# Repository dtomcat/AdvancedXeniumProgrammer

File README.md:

# OpenXenium JTAG and Flash Memory Chip programmer

**This is based on work done by [kooscode](https://github.com/kooscode/xenium-programmer) and [Ryzee119](https://github.com/ryzee119/openxenium) with modifications to program the bare ICs.  Most of the code here was done by kooscode (please visit the link above).

--------------

## * Read: ["Home Brew" on ORIGINAL XBOX](XBOX.md) - a detailed article on why and how *

The tools in this repo will allow you to use a Raspberry PI to program the CPLD and Flash Memory chips of the OpenXenium via Jtag and a custom 4-bit bus NOR Flash programming protocol.
Original project mentioned above allowed the use of an Onion Omega2+... This has been removed for this project. 

### Raspberry PI:
- This has only been tested on PI Zero W and PI 3B+ models so far.

https://www.pishop.us/product/raspberry-pi-zero-w/

-------------
## INSTALLING THE XENIUM PROGRAMMER
**The scripts assumes user of "pi"...  if using a different user, you'll need to manually change "pi" to your username in the scripts**
- After the OS has been written to your SD card, insert SD card into PC.
    - Add the following to the last line in "config.txt":   `enable_uart=1`
        - This is required to allow the PWR LED to function properly.
- Save edit and eject SD Card.  Insert SD card into Pi and boot up.
- Connect to the PI via SSH or Serial terminal
- If git is not installed, you need to install it:
    - `sudo apt-get install git`
- Clone this repo by running: `git clone https://github.com/dtomcat/AdvancedXeniumProgrammer.git`
- Change to program directory: `cd AdvancedXeniumProgrammer`
- Fix permission on install file:  `chmod 755 install`
- Then run: `./install`
- Setup service to listen for button presses:
    - `sudo cp xenium.service /etc/systemd/system/xenium.service`
    - `sudo systemctl daemon-reload`
    - `sudo systemctl enable xenium`
    - `sudo service xenium start`

## UPDATING XENIUM PROGRAMMER

- Connect to the PI via SSH or Serial terminal 
- Pull the latest code with: `git pull`
- Then run: `./install` 

-------------
## STATUS LED MEANING (From top to bottom)

- First:  Programming CPLD with BIT BANG firmware
- Second: Programming Flash with specified OS
- Third:  Verifying flash was programmed successfully
- Forth:  Programing CPLD with OpenXenium firmware

-------------
## PROGRAMMING THE XENIUM CPLD AND/OR FLASH MEMORY (STANDALONE)

Note: You will need to provide your own PrometheOS bin file. (save it in the /xenium-bin folder as promOS.bin)

- After the PI has fully booted and the green led is on...
    - Press the FIRST button to program the OpenXenium with XeniumOS.
    - Hold the FIRST button to program the OpenXenium with PrometheOS.
    - Press the SECOND button to program the flash chip with XeniumOS. (**The CPLD must be programmed with the Bit Bang firmware or this will fail.)
    - Hold the SECOND button to program the flash chip with PrometheOS. (**The CPLD must be programmed with the Bit Bang firmware or this will fail.)
    - Press the THIRD button to program the CPLD with the OpenXenium Firmware.
    - Hold the THIRD button to program the CPLD with the BitBang Firmware.
    - Press the FOURTH button to clear any errors.
    - Hold the FOURTH button to shutdown the Raspberry Pi.

-------------
## PROGRAMMING THE XENIUM CPLD AND/OR FLASH MEMORY (SSH/SERIAL)
This is good to do if you keep getting an error trying to program the chips. (Red LED remains on)

Note: You will need to provide your own PrometheOS bin file. (save it in the /xenium-bin folder as promOS.bin)

- Connect to the PI via SSH or Serial terminal
- Change dir to AdvancedXeniumProgrammer
- You can program CPLD and FLASH in one single step with XeniumOS (XOS).
    - Run: `./xenium-programmer-smd`
- You can program CPLD and FLASH in one single step with PrometheOS (PromOS).
    - Run: `./PromOS-programmer-smd`
- You can program just the CPLD in one two ways.
    - To program the Bit Bang firmware: 
        - Run: `./BitBangOnly`
    - To program the OpenXenium firmware: 
        - Run: `./OX-Only_SMD`
- You can program just the Flash in oe of two ways. (The CPLD MUST have the Bit Bang Firmware loaded)
    - To program XOS:
          - Run: `./FlashOnly`
    - To program PromOS:
          - Run: `./FlashOnlyProm`

-------------
### 3D PRINTED CASE

Just a quick and simple design I put together.  I'm sure this thing could be improved upon greatly.  Sharing for anyone wanting it.

NOTE:  for the "light pipes", I just used some clear PLA (2.90mm not standard 1.75) filament. 

--------------
### PC BOARD

Huge thanks to James Bolding for the Original Eagle PCB hardware design!
This PCB design is based on his original work.  

- You can use the FREE Eagle PCB to load this up or just use the gerber files to have the PCB made at OSH Park!

--------------

### PARTS NOT LISTED IN BOM
There are a couple parts not listed in BOM that could be helpful.
- Pin headers 2.54 spacing
    - 1 2x7 for LPC port
    - 1 1x2 for 3v3 (Optionally... but connect two points with solder)
        - Will need a 2-Pin Jumper/Bridge Cap if installing 1x2 pin header
- 6 Pogo pins (P75-E3 pogo pins seem to work the best)

-------------
## CREDITS

- Koos du Preez - Creator (kdupreez@hotmail.com - Comments, improvements, critique, etc. is welcome!)
- Dtomcat - SMD programmer PCB design and code split to allow status LEDs.
- James Bolding - Orignal hardware design and PCB!
- Ryzee119 -  OpenXenium Firmware and hardware and all round awesomeness!
- XC3SPROG - Not sure who to thank here, but the source code was pivotal in making this work!

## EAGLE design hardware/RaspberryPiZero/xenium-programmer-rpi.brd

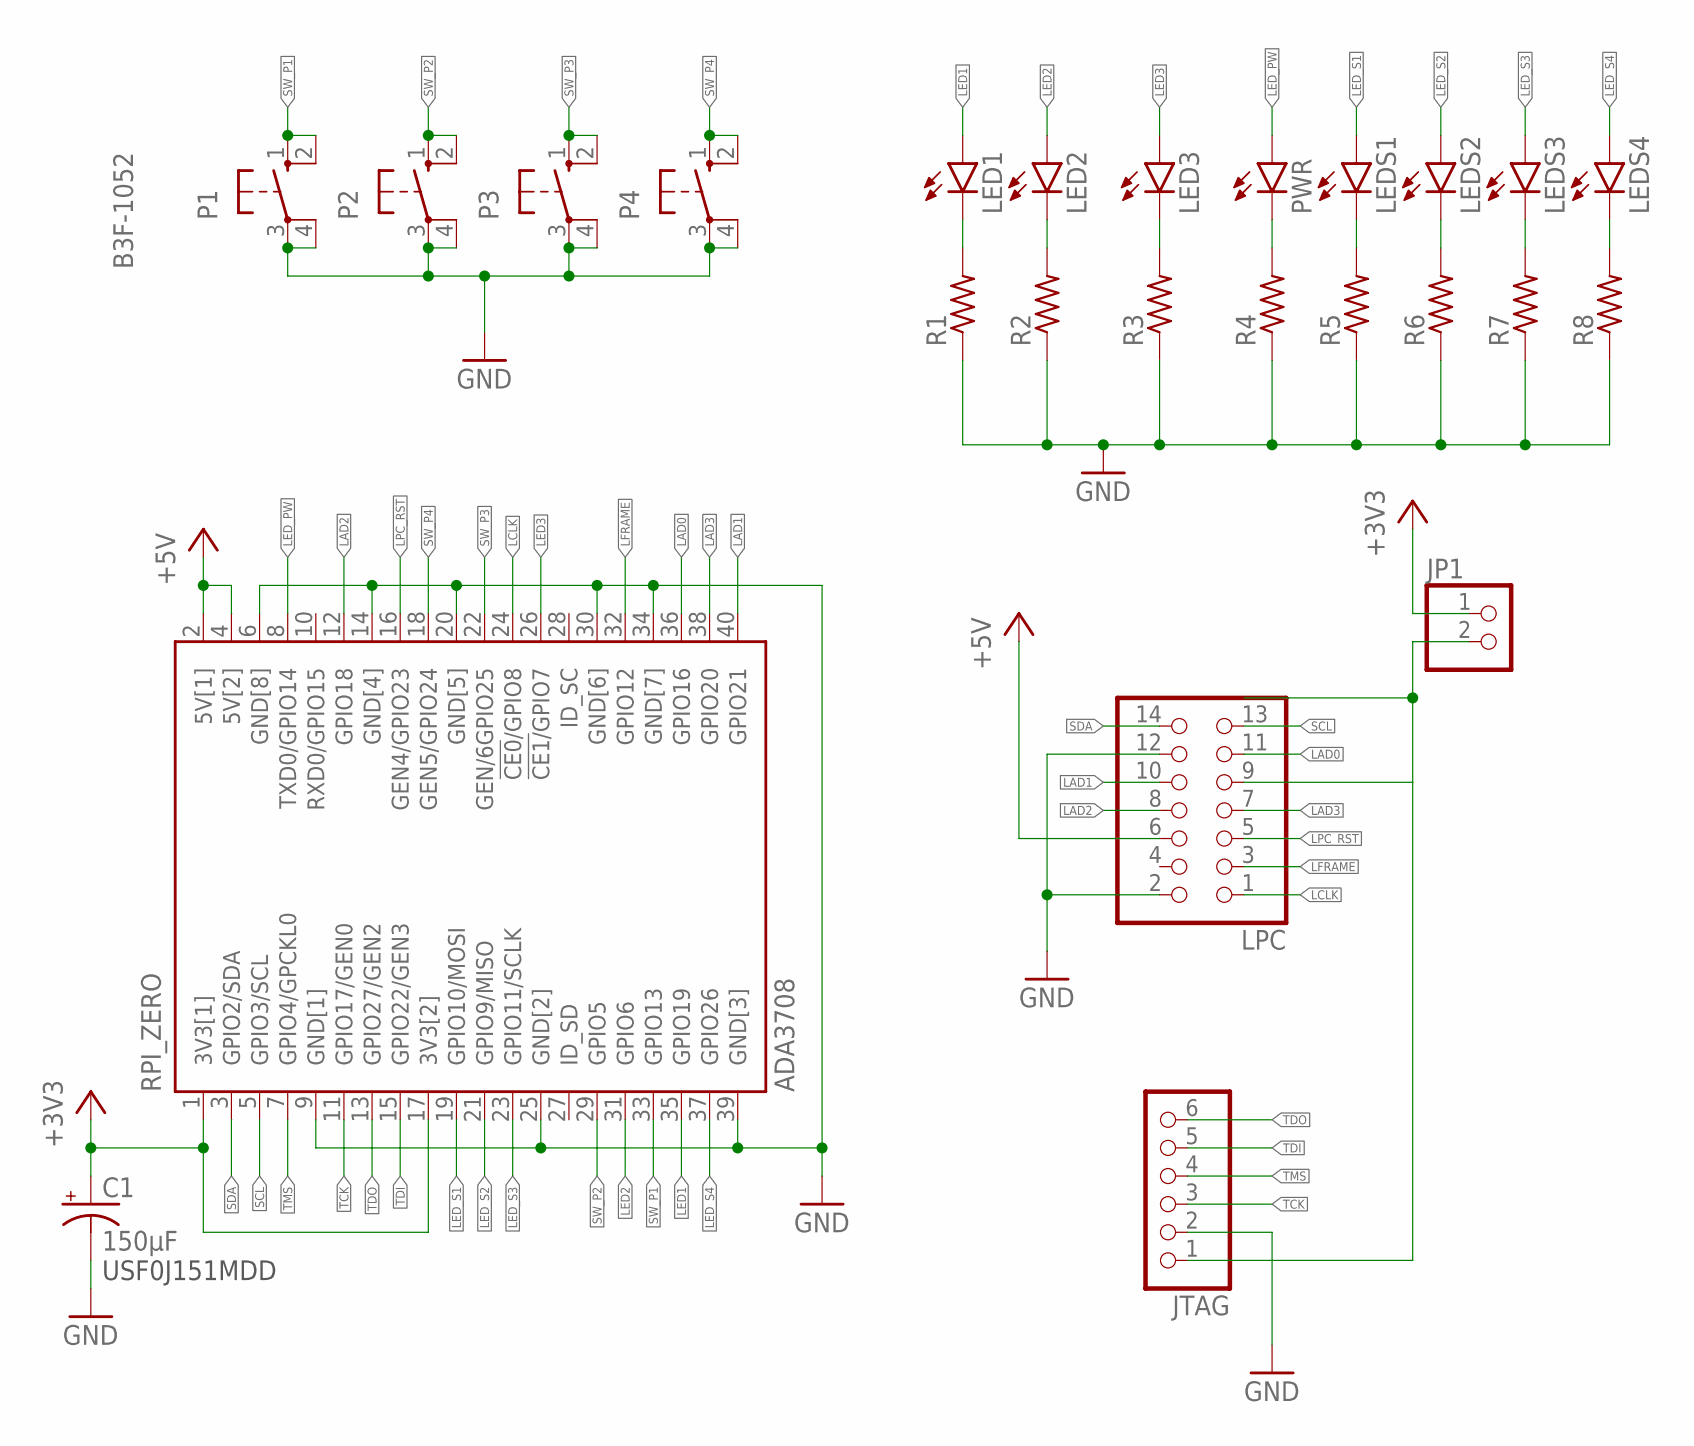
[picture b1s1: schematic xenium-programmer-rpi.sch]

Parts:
C1: 150µF; E3,5-8
JP1: PINHD-1X2; 1X02
JTAG: PINHD-1X6; 1X06
LED1, LED2, LED3: LEDCHIPLED_1206; CHIPLED_1206
LEDS1, LEDS2, LEDS3, LEDS4: LEDCHIPLED_1206; CHIPLED_1206
LPC: PINHD-2X7; 2X07
P1, P2, P3, P4: B3F-1052; B3F-10XX
PWR: LEDCHIPLED_1206; CHIPLED_1206
R1, R2, R3, R4, R5, R6, R7, R8: R-US_R1206; R1206
RPI_ZERO: ADA3708; ADA3708_RPI-ZERO

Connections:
+3V3: C1.+, JP1.1, RPI_ZERO.1 (3V3[1]), RPI_ZERO.17 (3V3[2])
+5V: LPC.6, RPI_ZERO.2 (5V[1]), RPI_ZERO.4 (5V[2])
GND: C1.-, JTAG.2, LPC.2, LPC.12, P1.3, P1.4 (P1), P2.3, P2.4 (P1), P3.3, P3.4 (P1), P4.3, P4.4 (P1), R1.1, R2.1, R3.1, R4.1, R5.1, R6.1, R7.1, R8.1, RPI_ZERO.6 (GND[8]), RPI_ZERO.9 (GND[1]), RPI_ZERO.14 (GND[4]), RPI_ZERO.20 (GND[5]), RPI_ZERO.25 (GND[2]), RPI_ZERO.30 (GND[6]), RPI_ZERO.34 (GND[7]), RPI_ZERO.39 (GND[3])
LAD0: LPC.11, RPI_ZERO.36 (GPIO16)
LAD1: LPC.10, RPI_ZERO.40 (GPIO21)
LAD2: LPC.8, RPI_ZERO.12 (GPIO18)
LAD3: LPC.7, RPI_ZERO.38 (GPIO20)
LCLK: LPC.1, RPI_ZERO.24 (!CE0!/GPIO8)
LED1: LED1.A, RPI_ZERO.35 (GPIO19)
LED2: LED2.A, RPI_ZERO.31 (GPIO6)
LED3: LED3.A, RPI_ZERO.26 (!CE1/!GPIO7)
LED_PW: PWR.A, RPI_ZERO.8 (TXD0/GPIO14)
LED_S1: LEDS1.A, RPI_ZERO.19 (GPIO10/MOSI)
LED_S2: LEDS2.A, RPI_ZERO.21 (GPIO9/MISO)
LED_S3: LEDS3.A, RPI_ZERO.23 (GPIO11/SCLK)
LED_S4: LEDS4.A, RPI_ZERO.37 (GPIO26)
LFRAME: LPC.3, RPI_ZERO.32 (GPIO12)
LPC_RST: LPC.5, RPI_ZERO.16 (GEN4/GPIO23)
unnamed: LED1.C, R1.2
unnamed: LED2.C, R2.2
unnamed: LED3.C, R3.2
unnamed: PWR.C, R4.2
unnamed: JP1.2, JTAG.1, LPC.9
unnamed: LEDS1.C, R5.2
unnamed: LEDS2.C, R6.2
unnamed: LEDS3.C, R7.2
unnamed: LEDS4.C, R8.2
SCL: LPC.13, RPI_ZERO.5 (GPIO3/SCL)
SDA: LPC.14, RPI_ZERO.3 (GPIO2/SDA)
SW_P1: P1.1 (S), P1.2 (S1), RPI_ZERO.33 (GPIO13)
SW_P2: P2.1 (S), P2.2 (S1), RPI_ZERO.29 (GPIO5)
SW_P3: P3.1 (S), P3.2 (S1), RPI_ZERO.22 (GEN/6GPIO25)
SW_P4: P4.1 (S), P4.2 (S1), RPI_ZERO.18 (GEN5/GPIO24)
TCK: JTAG.3, RPI_ZERO.11 (GPIO17/GEN0)
TDI: JTAG.5, RPI_ZERO.15 (GPIO22/GEN3)
TDO: JTAG.6, RPI_ZERO.13 (GPIO27/GEN2)
TMS: JTAG.4, RPI_ZERO.7 (GPIO4/GPCKL0)

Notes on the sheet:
USF0J151MDD

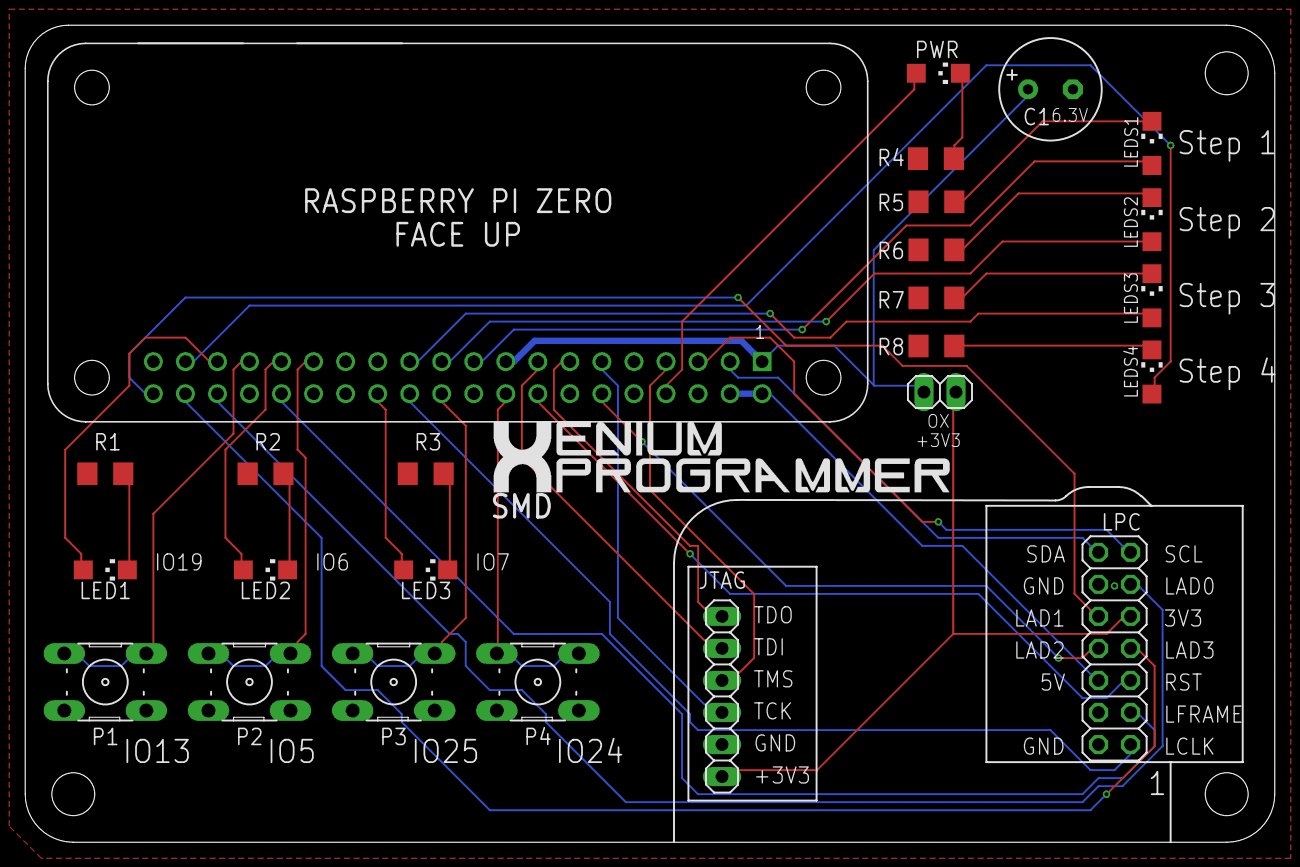
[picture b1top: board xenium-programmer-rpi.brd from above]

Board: 2 copper layers, 99.1 x 64.8 mm, 25 parts (0 on the bottom side), 37 nets.

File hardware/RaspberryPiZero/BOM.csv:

Reference,Qty,Description,Part Number,Manufacturer,Digikey
"R1,R2,R3,R5,R6,R7,R8",7,RES 68 OHM 1% 1/4W 1206,RC1206FR-1068RL,YAGEO,13-RC1206FR-1068RLCT-ND
R4,1,RES 15 OHM 1% 1/4W 1206,RC1206FR-1015RL,YAGEO,13-RC1206FR-1015RLCT-ND
PWR,1,LED BLUE CLEAR 1206 SMD,LTST-C150TBKT,Lite-On Inc.,160-1643-1-ND
LED1,1,LED GREEN CLEAR 1206 SMD,LTST-C150KGKT,Lite-On Inc.,160-1404-1-ND
LED2,1,LED YELLOW CLEAR 1206 SMD,LTST-C150KSKT,Lite-On Inc.,160-1406-1-ND
LED3,1,LED RED CLEAR 1206 SMD,LTST-C150KRKT,Lite-On Inc.,160-1405-1-ND
"LEDS1,LEDS2,LEDS3,LEDS4",4,LED ORANGE CLEAR 1206 SMD,LTST-C150KFKT,Lite-On Inc.,160-1403-1-ND
C1,1,CAP ALUM 150UF 20% 6.3V RADIAL,UPW0J151MED,Nichicon,493-1698-ND
"P1,P2,P3,P4",4,SWITCH TACTILE SPST-NO 0.05A 24V,1825910-6,TE Connectivity ALCOSWITCH Switches,450-1650-ND
RPI-CONN,1,CONN HDR 40POS 0.1 TIN PCB,PPTC202LFBN-RC,Sullins Connector Solutions,S6104-ND

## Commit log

2024-03-17 Initial
    Initial Upload
2024-03-17 punctuation
2024-05-09 Add 3d printed case and explain status LEDs
2024-05-09 updated link to image
2024-05-09 Put 3D Case into folder
2024-05-29 Update install to use github wiringpi
    The version of wiringpi included from the old link is showing up as incompatible with the Rasberry Pi zero 2, maybe it's a good idea to make sure this doesn't break the zero 1 before we push this
2024-05-29 Update xenium.service to output to journal
    Was having an issue with a headless version of raspbian OS where it was not logging phython3 output
2026-01-09 Update install
    Implemented a fix for wiringpi since drogon.net took it offline.

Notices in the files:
hardware/RaspberryPiZero/xenium-programmer-rpi.brd:
Released under
CERN OHL v1.2
